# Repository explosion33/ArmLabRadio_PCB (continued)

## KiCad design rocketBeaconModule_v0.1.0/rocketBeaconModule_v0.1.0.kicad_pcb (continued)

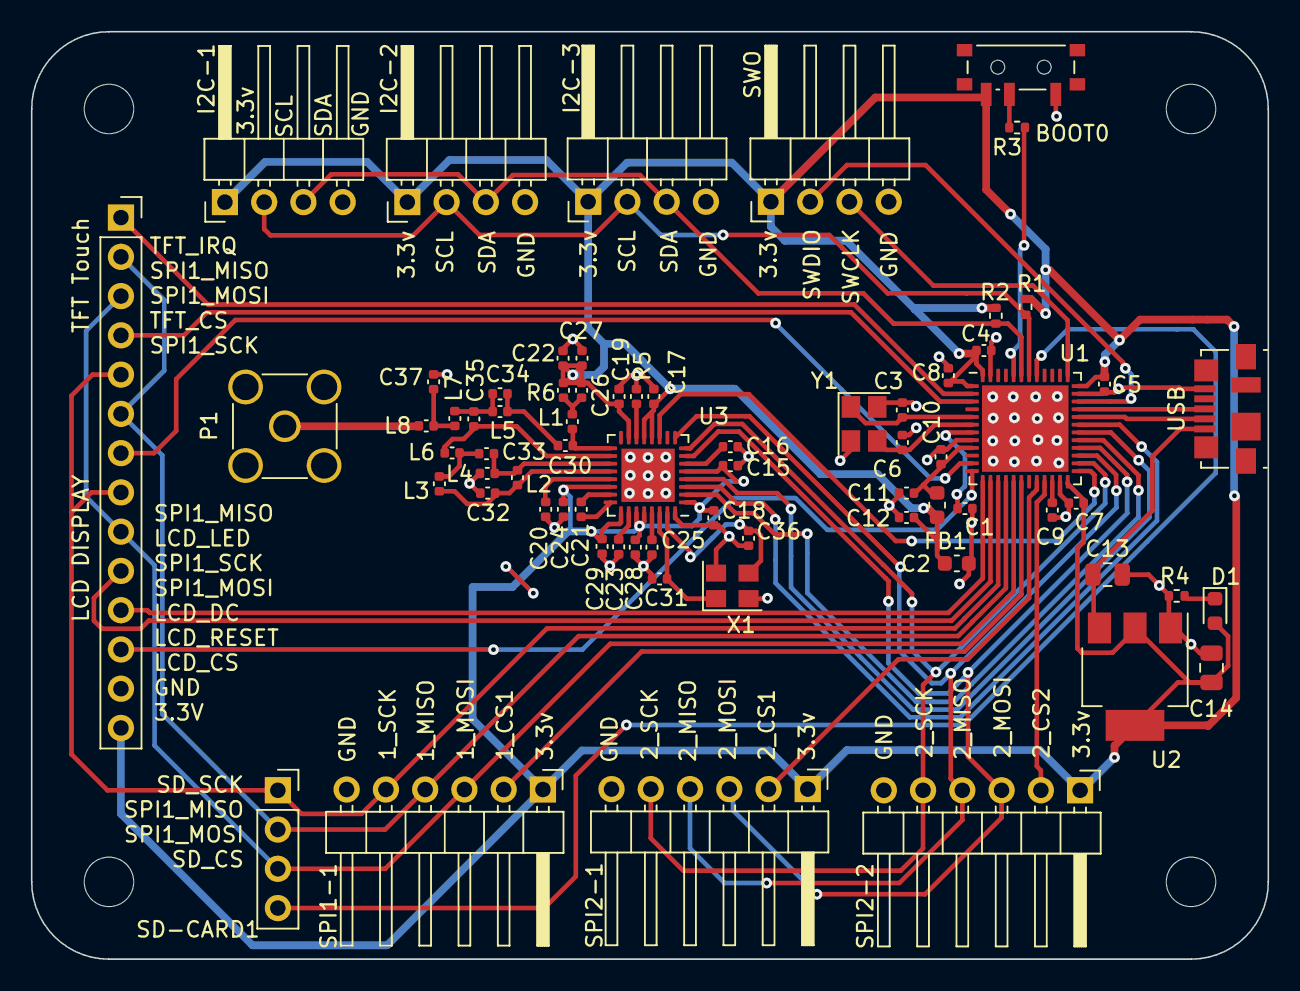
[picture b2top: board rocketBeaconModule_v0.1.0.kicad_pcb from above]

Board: 2 copper layers, 80.0 x 60.0 mm, 74 parts (0 on the bottom side), 56 nets.

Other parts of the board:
BOOT0: SW_SPDT; SW_SPDT_PCM12
SWO: SWO; PinHeader_1x04_P2.54mm_Horizontal
USB: USB_B_Micro; USB_Micro-B_Molex_47346-0001

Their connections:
+3.3V: BOOT0.3 (C), SWO.1; also elsewhere on the board
/SWCLK: SWO.3; also elsewhere on the board
/SWDIO: SWO.2; also elsewhere on the board
/SW_BOOT0: BOOT0.2 (B); also elsewhere on the board
/USB_D+: USB.3 (D+); also elsewhere on the board
/USB_D-: USB.2 (D-); also elsewhere on the board
GND: BOOT0.1 (A), SWO.4, USB.5 (GND); also elsewhere on the board
VBUS: USB.1 (VBUS); also elsewhere on the board

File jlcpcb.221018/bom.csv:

Designator,Footprint,Quantity,Value,LCSC Part #
C4,C_0402_1005Metric,1,100n,
C10,C_0402_1005Metric,1,10n,
C18,C_0402_1005Metric,1,47nF,
C7,C_0402_1005Metric,1,100n,
P1,SMA_Amphenol_132134-11_Vertical,1,AntMount,
R6,R_0402_1005Metric,1,1k,
D1,LED_0603_1608Metric,1,LED,
R7,R_0402_1005Metric,1,1k,
R4,R_0402_1005Metric,1,5.11k,
C26,C_0402_1005Metric,1,56pF,
C29,C_0402_1005Metric,1,47nF,
C32,C_0402_1005Metric,1,5.1pF,
C22,C_0402_1005Metric,1,10nF,
C6,C_0402_1005Metric,1,10p,
C21,C_0402_1005Metric,1,1.8nF,
L5,C_0402_1005Metric,1,15nH,
FB1,L_0603_1608Metric,1,120R,
R3,R_0402_1005Metric,1,5.11k,
C19,C_0402_1005Metric,1,47nF,
C12,C_0402_1005Metric,1,1u,
J1,HRO_TYPE-C-31-M-12,1,TYPE-C-31-M-12,
C23,C_0402_1005Metric,1,47nF,
R5,R_0402_1005Metric,1,1k,
U1,QFN-48-1EP_7x7mm_P0.5mm_EP5.6x5.6mm,1,STM32F401CCU6,
L7,C_0402_1005Metric,1,43nH,
C9,C_0402_1005Metric,1,2.2u,
C15,C_0402_1005Metric,1,47nF,
C24,C_0402_1005Metric,1,47nF,
L2,C_0402_1005Metric,1,56nH,
U3,QFN-32-1EP_5x5mm_P0.5mm_EP3.45x3.45mm,1,CC1200,
D2,LED_0603_1608Metric,1,LED,
H4,MountingHole_3.2mm_M3,1,MountingHole,
L6,C_0402_1005Metric,1,15nH,
C25,C_0402_1005Metric,1,47nF,
C11,C_0402_1005Metric,1,1u,
C31,C_0402_1005Metric,1,10pF,
C34,C_0402_1005Metric,1,2.2pF,
C36,C_0402_1005Metric,1,10pF,
J2,PinSocket_1x04_P2.54mm_Vertical,1,MODE,
C28,C_0402_1005Metric,1,47nF,
C8,C_0402_1005Metric,1,100n,
X1,Oscillator_SMD_Abracon_ASE-4Pin_3.2x2.5mm,1,40mhz,
C17,C_0402_1005Metric,1,47nF,
C1,C_0402_1005Metric,1,100n,
C16,C_0402_1005Metric,1,0.22 uF,
D3,LED_0603_1608Metric,1,LED,
R9,C_0402_1005Metric,1,18,
C14,C_0805_2012Metric,1,22u,
C5,C_0402_1005Metric,1,100n,
SWD1,PinHeader_1x04_P2.54mm_Vertical,1,FLASH,
C33,C_0402_1005Metric,1,5.1pF,
Y1,Crystal_SMD_3225-4Pin_3.2x2.5mm,1,16MHz,
L3,C_0402_1005Metric,1,27nH,
C37,C_0402_1005Metric,1,6.2pF,
H2,MountingHole_3.2mm_M3,1,MountingHole,
L4,C_0402_1005Metric,1,27nH,
R1,R_0402_1005Metric,1,1.5k,
R2,R_0402_1005Metric,1,1.5k,
C30,C_0402_1005Metric,1,39pF,
J3,PinSocket_1x07_P2.54mm_Vertical,1,Main Bus,
H3,MountingHole_3.2mm_M3,1,MountingHole,
C3,C_0402_1005Metric,1,10p,
C35,C_0402_1005Metric,1,5.1pF,
L8,C_0402_1005Metric,1,22nH,
C20,C_0402_1005Metric,1,10nF,
C2,C_0603_1608Metric,1,10u,
U2,SOT-223-3_TabPin2,1,AMS1117-3.3,
R8,C_0402_1005Metric,1,56k,
C13,C_0805_2012Metric,1,22u,
H1,MountingHole_3.2mm_M3,1,MountingHole,
L1,C_0402_1005Metric,1,56nH,
C27,C_0402_1005Metric,1,100pF,

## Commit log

2022-10-18 Initial radiobeacon designs
2022-10-19 fixed usb / io footprint mixup
2022-10-19 removed old footprints and replaced with new ones
2022-10-19 DRC resolution on PCB layouts
2022-10-19 updated silk screen\nincreased spacing between leds\nchanged version number to 2.0
2022-10-19 Set Version 1.1
2022-10-19 backup v1.1; add part numbers
2022-10-19 add v1.1 image
2024-08-09 V3 changes
2024-08-09 added power pads
2024-08-09 v3 pic
2024-09-06 Added larger 60mm cutout to match rocket club *note this is not nescesary since mounting holes line up between both sizes, it would be purely aesthetic
2024-09-30 V4 Changes Added SKYWORKS +30db 4W FEM Added LM2576 3.9V supply Increased diameter to 60mm Re-routed full board
2024-09-30 Adjusted some component footprints and part numbers Increased size of inductor and repositioned generated gbrs, drills, bom and cpl (up to date)
2024-11-14 switched pins on ribbon cable to connect evenly with FC when flipped
2025-04-26 removed old PA
2025-04-27 checked matching network on CC1200 schematic
2025-04-28 completed most of radio schematic
2025-04-28 changed rf switch, updated rf amp footprint and updated schematic
2025-04-30 fixed temp sensor and updated digpot stm32 connections
2025-04-30 added decoupling capacitor to dpot and changed RTD1000 to RTD100
2025-04-30 reference/backup for mostly routed pcb
2025-04-30 finished majority of routing other than matching network and amplifier/switch/antenna
2025-05-01 finished routing pcb and passed DRC, waiting for review by Ethan
2025-05-01 Revert "Stephen"
2025-05-01 added Mitsibushi Amp w/ supporting gate control circuitry, switching, and temperature monitoring
2025-05-02 BOM fixes and manufactureing files
